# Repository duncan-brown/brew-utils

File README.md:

# brew-utils

Software for a homebrewery dashboard built out of Knight Rider (KITT) dash
replica hardware.

Two Raspberry Pis read temperature probes, flow meters, fermentation
controllers and a keg-monitoring database, and render all of it onto the gauges
of a replica KITT dashboard: the MPH display shows hot liquor tank temperature,
the RPM gauges show serving keezer probes, the LED bargraphs show fermenter
temperatures and how much beer is left in each keg, and the message center
captions whatever the multi-function display is currently showing.

There is a full build write-up, with photos of what every gauge means, at
[Brewery Dashboard on HomebrewTalk](https://www.homebrewtalk.com/threads/brewery-dashboard.726917/).
The physical side — power supply, relays, probes, which wire goes to which pin
on which Pi — is in [HARDWARE.md](HARDWARE.md).

## How it fits together

```
    probes, flow meters, kegs                two Raspberry Pis            KITT dash
    ─────────────────────────                ─────────────────            ─────────
    DS18B20 one-wire probes  ──────────────▶  rpints  ──── serial ────▶  tacho
    RaspberryPints (MySQL)   ──────────────▶          ──── serial ────▶  dummy3, dummy6
                                                 │
                                            GPIO │ mode
                                                 ▼
    DS18B20 one-wire probes  ──────────────▶  brewpi  ──── serial ────▶  speedo
    BrewPi Remix ◀── TiltBridge ◀── Tilt ──▶          ──── serial ────▶  message center
    flow meter relays        ◀──────────────
```

- **`rpints`** runs [RaspberryPints](https://github.com/RaspberryPints/RaspberryPints)
  for keg volume tracking, and owns the dashboard's Power/Auto/Norm/Pursuit
  buttons and the power relays for the whole dash.
- **`brewpi`** runs three instances of [BrewPi Remix](https://github.com/brewpi-remix/brewpi-tools-rmx)
  for fermentation control, which get specific-gravity readings from Tilt
  hydrometers via [TiltBridge](https://github.com/thorrak/tiltbridge).
- The two Pis coordinate over GPIO lines so that pressing Auto, Norm or Pursuit
  on one changes what the other displays and how brightly.
- Both drive the dash boards over serial using Paolo Sancono's KITT protocol.
  The dash electronics themselves are from [ideegeniali](https://www.ideegeniali.it/).

## What's in here

| Path | Status | Description |
| --- | --- | --- |
| [`kitt/`](kitt/) | **in service** | The current system. `panp/panp.py` drives the whole dashboard; `switchpod/` is the Arduino firmware for the dash keypads. See [kitt/README.md](kitt/README.md) for how it works, and [kitt/DASHBOARD.md](kitt/DASHBOARD.md) for what each gauge means. |
| [`schematics/`](schematics/) | reference | KiCad schematics of the control electronics, four sheets generated from the wiring in `HARDWARE.md`; rendered as `images/schematic-*.svg`. |
| `brewpitosmith` | utility | Converts a BrewPi Remix beer log into a CSV that BeerSmith 3 will import, thinned to one row an hour. |
| `images/` | reference | Photographs of the switch pods, the season 2 dash scan, and the `hw-*` photographs of the bench, supply box and control panel that [HARDWARE.md](HARDWARE.md) refers to. |

Two earlier efforts have been archived out of the tree. Each is tagged, so the
whole thing comes back with one command:

| Tag | What it was |
| --- | --- |
| `karr-prototype` | An attempt to rebuild the dash electronics from scratch — four ESP32s driving daisy-chained TLC5940 drivers, with a KiCad board and gerbers. Shelved in 2023 when the ideegeniali boards arrived; never ran the brewery. |
| `pi-temp-display-final` | The predecessor to the KITT dash: seven-segment LEDs multiplexed with pigpio, showing mash temperature and keezer min/max. |

```bash
git checkout karr-prototype -- karr/
```

## Credits

The parts of this system that do the actual work of running the brewery are
other people's: BrewPi Remix by [@LBussy](https://github.com/lbussy), TiltBridge
by [@Thorrak](https://github.com/thorrak), RaspberryPints by
[@RandR+](https://github.com/RandRPints), and the KITT dash boards and serial
protocol by Paolo Sancono at ideegeniali. Thanks also to @day_trippr for help
along the way.

## License

MIT — see [LICENSE](LICENSE).

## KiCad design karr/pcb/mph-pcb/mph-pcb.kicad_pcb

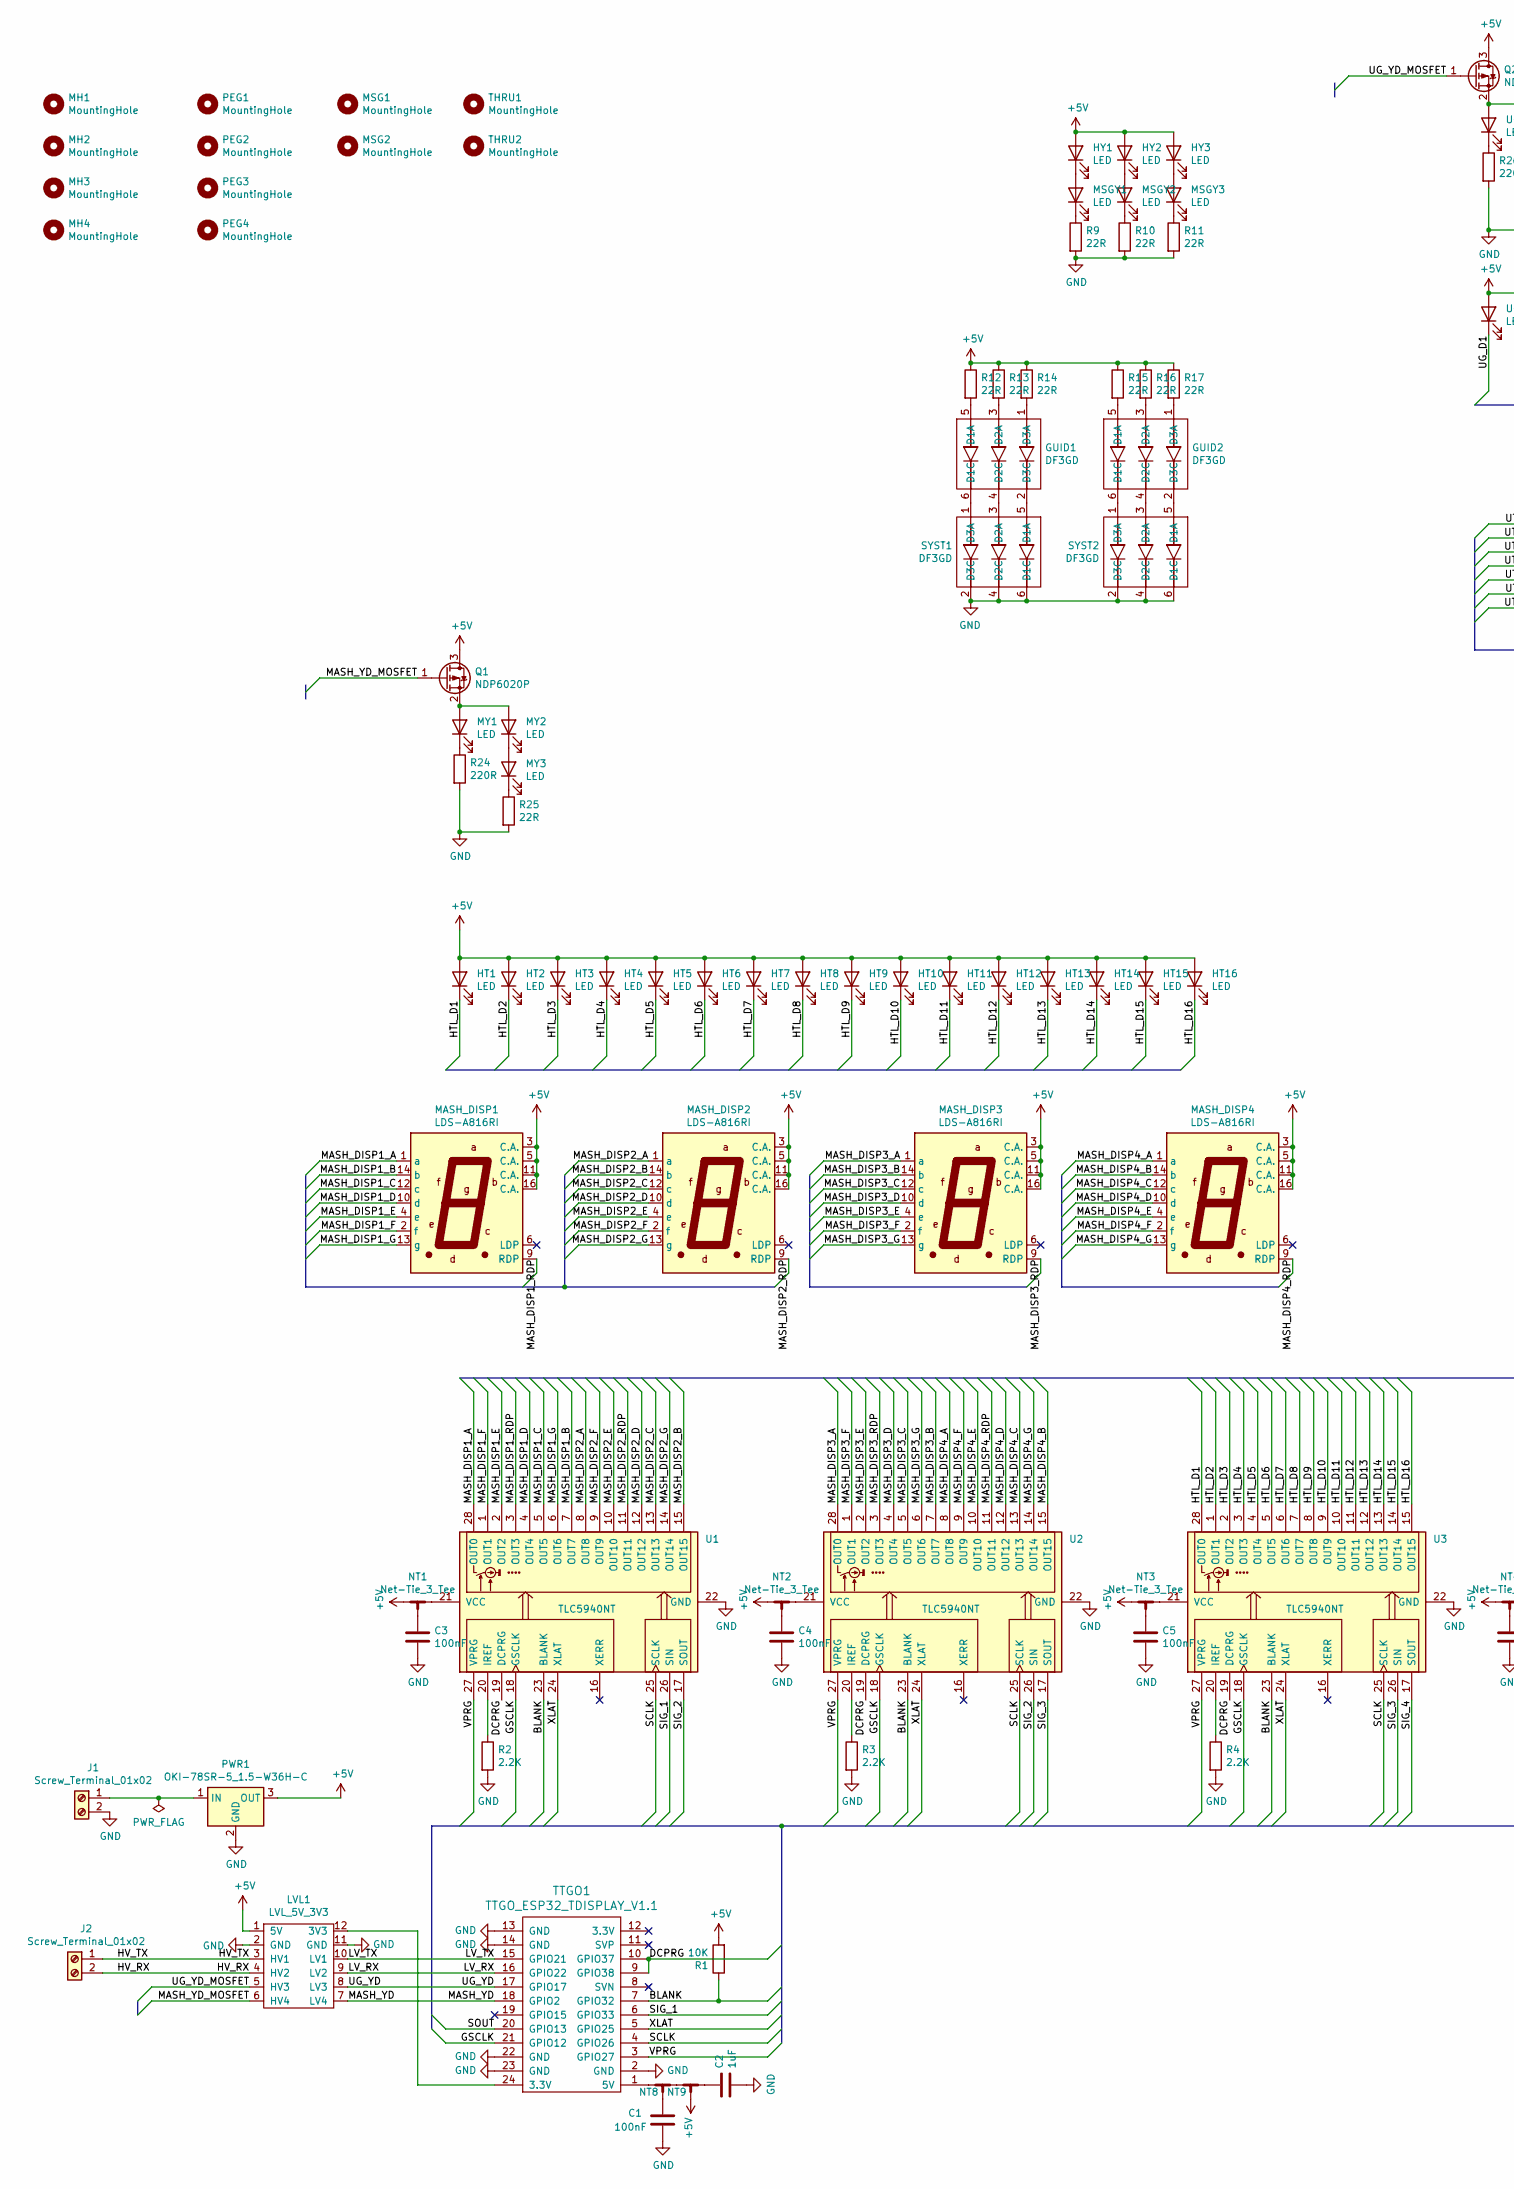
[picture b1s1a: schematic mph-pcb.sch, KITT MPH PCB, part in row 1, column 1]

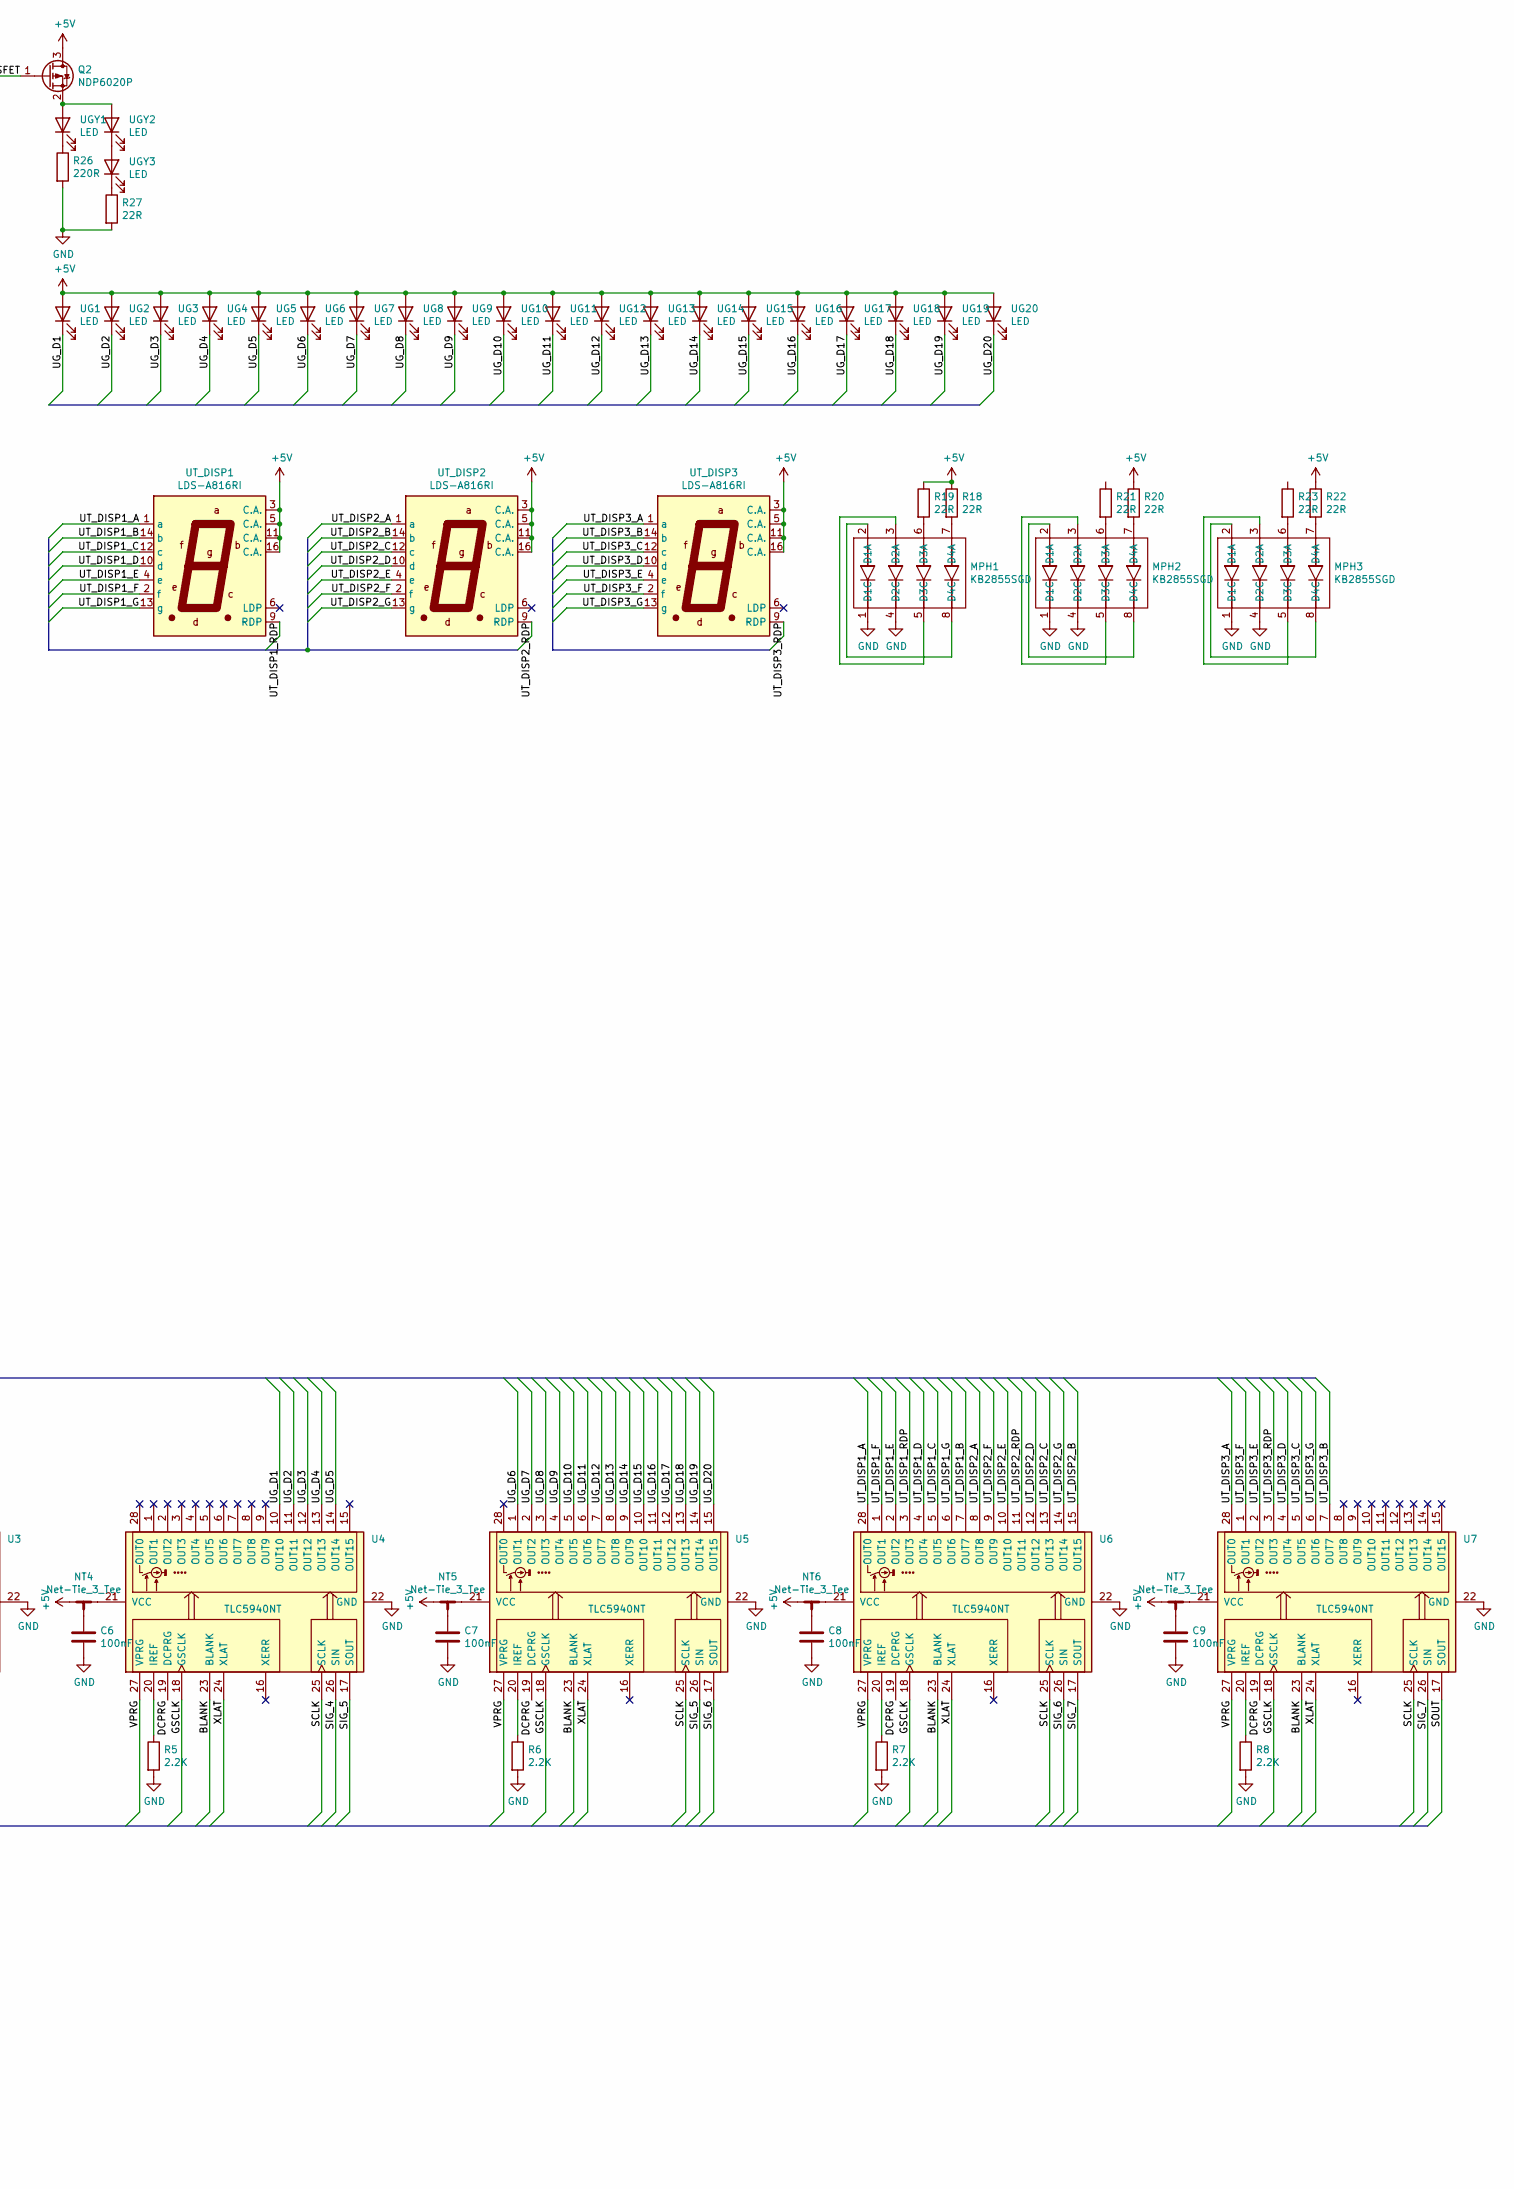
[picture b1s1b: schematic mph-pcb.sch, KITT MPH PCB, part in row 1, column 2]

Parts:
C1, C3, C4, C5, C6, C7, C8, C9: 100nF; C_Rect_L7.0mm_W3.5mm_P5.00mm
C2: 1uF; C_Rect_L7.0mm_W3.5mm_P5.00mm
GUID1, GUID2: DF3GD; DF3GD_Light_Bar
HT1, HT2, HT3, HT4, HT5, HT6, HT7, HT8, HT9, HT10, HT11, HT12, HT13, HT14, HT15, HT16: LED; Flangeless_LED
HY1, HY2, HY3: LED; Flangeless_LED
J1, J2: Screw_Terminal_01x02; 5mm_Screw_Terminal_01x02
LVL1: LVL_5V_3V3
MASH_DISP1, MASH_DISP2, MASH_DISP3, MASH_DISP4: LDS-A816RI
MH1, MH2, MH3, MH4: MountingHole; MountingHole_3.2mm_M3
MPH1, MPH2, MPH3: KB2855SGD; KB2855SGD_Light_Square
MSG1, MSG2: MountingHole; MountingHole_3.2mm_M3
MSGY1, MSGY2, MSGY3: LED; Flangeless_LED
MY1, MY2, MY3: LED; Flangeless_LED
NT1, NT2, NT3, NT4, NT5, NT6, NT7, NT8, NT9: Net-Tie_3_Tee; NetTie-3_THT_Pad0.3mm
PEG1, PEG2, PEG3, PEG4: MountingHole; MountingHole_5.3mm_M5
PWR1: OKI-78SR-5_1.5-W36H-C; Converter_DCDC_muRata_OKI-78SR_Horizontal
Q1, Q2: NDP6020P; TO-220-3_Horizontal_TabDown
R1: 10K; R_Axial_DIN0207_L6.3mm_D2.5mm_P10.16mm_Horizontal
R2, R3, R4, R5, R6, R7, R8: 2.2K; R_Axial_DIN0207_L6.3mm_D2.5mm_P10.16mm_Horizontal
R9, R10, R11, R12, R13, R14, R15, R16, R17, R18, R19, R20, R21, R22, R23, R25, R27: 22R; R_Axial_DIN0207_L6.3mm_D2.5mm_P10.16mm_Horizontal
R24, R26: 220R; R_Axial_DIN0207_L6.3mm_D2.5mm_P10.16mm_Horizontal
SYST1, SYST2: DF3GD; DF3GD_Light_Bar
THRU1, THRU2: MountingHole; MountingHole_6.4mm_M6
TTGO1: TTGO_ESP32_TDISPLAY_V1.1; TTGO_ESP32_TDisplay_v1.1
U1, U2, U3, U4, U5, U6, U7: TLC5940NT; DIP-28_W7.62mm
UG1, UG2, UG3, UG4, UG5, UG6, UG7, UG8, UG9, UG10, UG11, UG12, UG13, UG14, UG15, UG16, UG17, UG18, UG19, UG20: LED; Flangeless_LED
UGY1, UGY2, UGY3: LED; Flangeless_LED
UT_DISP1, UT_DISP2, UT_DISP3: LDS-A816RI

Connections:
+5V: HT1.2 (A), HT2.2 (A), HT3.2 (A), HT4.2 (A), HT5.2 (A), HT6.2 (A), HT7.2 (A), HT8.2 (A), HT9.2 (A), HT10.2 (A), HT11.2 (A), HT12.2 (A), HT13.2 (A), HT14.2 (A), HT15.2 (A), HT16.2 (A), HY1.2 (A), HY2.2 (A), HY3.2 (A), LVL1.1 (5V), MASH_DISP1.3 (C.A.), MASH_DISP1.5 (C.A.), MASH_DISP1.11 (C.A.), MASH_DISP1.16 (C.A.), MASH_DISP2.3 (C.A.), MASH_DISP2.5 (C.A.), MASH_DISP2.11 (C.A.), MASH_DISP2.16 (C.A.), MASH_DISP3.3 (C.A.), MASH_DISP3.5 (C.A.), MASH_DISP3.11 (C.A.), MASH_DISP3.16 (C.A.), MASH_DISP4.3 (C.A.), MASH_DISP4.5 (C.A.), MASH_DISP4.11 (C.A.), MASH_DISP4.16 (C.A.), NT1.1, NT2.1, NT3.1, NT4.1, NT5.1, NT6.1, NT7.1, NT9.3, PWR1.3 (OUT), Q1.3 (D), Q2.3 (D), R1.2, R12.1, R13.1, R14.1, R15.1, R16.1, R17.1, R18.1, R19.1, R20.1, R22.1, UG1.2 (A), UG2.2 (A), UG3.2 (A), UG4.2 (A), UG5.2 (A), UG6.2 (A), UG7.2 (A), UG8.2 (A), UG9.2 (A), UG10.2 (A), UG11.2 (A), UG12.2 (A), UG13.2 (A), UG14.2 (A), UG15.2 (A), UG16.2 (A), UG17.2 (A), UG18.2 (A), UG19.2 (A), UG20.2 (A), UT_DISP1.3 (C.A.), UT_DISP1.5 (C.A.), UT_DISP1.11 (C.A.), UT_DISP1.16 (C.A.), UT_DISP2.3 (C.A.), UT_DISP2.5 (C.A.), UT_DISP2.11 (C.A.), UT_DISP2.16 (C.A.), UT_DISP3.3 (C.A.), UT_DISP3.5 (C.A.), UT_DISP3.11 (C.A.), UT_DISP3.16 (C.A.)
/BLANK: R1.1, TTGO1.7 (GPIO32), U1.23 (BLANK), U2.23 (BLANK), U3.23 (BLANK), U4.23 (BLANK), U5.23 (BLANK), U6.23 (BLANK), U7.23 (BLANK)
/DCPRG: TTGO1.9 (GPIO38), TTGO1.10 (GPIO37), U1.19 (DCPRG), U2.19 (DCPRG), U3.19 (DCPRG), U4.19 (DCPRG), U5.19 (DCPRG), U6.19 (DCPRG), U7.19 (DCPRG)
/GSCLK: TTGO1.21 (GPIO12), U1.18 (GSCLK), U2.18 (GSCLK), U3.18 (GSCLK), U4.18 (GSCLK), U5.18 (GSCLK), U6.18 (GSCLK), U7.18 (GSCLK)
/HTL_D1: HT1.1 (K), U3.28 (OUT0)
/HTL_D2: HT2.1 (K), U3.1 (OUT1)
/HTL_D3: HT3.1 (K), U3.2 (OUT2)
/HTL_D4: HT4.1 (K), U3.3 (OUT3)
/HTL_D5: HT5.1 (K), U3.4 (OUT4)
/HTL_D6: HT6.1 (K), U3.5 (OUT5)
/HTL_D7: HT7.1 (K), U3.6 (OUT6)
/HTL_D8: HT8.1 (K), U3.7 (OUT7)
/HTL_D9: HT9.1 (K), U3.8 (OUT8)
/HTL_D10: HT10.1 (K), U3.9 (OUT9)
/HTL_D11: HT11.1 (K), U3.10 (OUT10)
/HTL_D12: HT12.1 (K), U3.11 (OUT11)
/HTL_D13: HT13.1 (K), U3.12 (OUT12)
/HTL_D14: HT14.1 (K), U3.13 (OUT13)
/HTL_D15: HT15.1 (K), U3.14 (OUT14)
/HTL_D16: HT16.1 (K), U3.15 (OUT15)
/HV_RX: J2.2, LVL1.4 (HV2)
/HV_TX: J2.1, LVL1.3 (HV1)
/LV_RX: LVL1.9 (LV2), TTGO1.16 (GPIO22)
/LV_TX: LVL1.10 (LV1), TTGO1.15 (GPIO21)
/MASH_DISP1_A: MASH_DISP1.1 (a), U1.28 (OUT0)
/MASH_DISP1_B: MASH_DISP1.14 (b), U1.7 (OUT7)
/MASH_DISP1_C: MASH_DISP1.12 (c), U1.5 (OUT5)
/MASH_DISP1_D: MASH_DISP1.10 (d), U1.4 (OUT4)
/MASH_DISP1_E: MASH_DISP1.4 (e), U1.2 (OUT2)
/MASH_DISP1_F: MASH_DISP1.2 (f), U1.1 (OUT1)
/MASH_DISP1_G: MASH_DISP1.13 (g), U1.6 (OUT6)
/MASH_DISP1_RDP: MASH_DISP1.9 (RDP), U1.3 (OUT3)
/MASH_DISP2_A: MASH_DISP2.1 (a), U1.8 (OUT8)
/MASH_DISP2_B: MASH_DISP2.14 (b), U1.15 (OUT15)
/MASH_DISP2_C: MASH_DISP2.12 (c), U1.13 (OUT13)
/MASH_DISP2_D: MASH_DISP2.10 (d), U1.12 (OUT12)
/MASH_DISP2_E: MASH_DISP2.4 (e), U1.10 (OUT10)
/MASH_DISP2_F: MASH_DISP2.2 (f), U1.9 (OUT9)
/MASH_DISP2_G: MASH_DISP2.13 (g), U1.14 (OUT14)
/MASH_DISP2_RDP: MASH_DISP2.9 (RDP), U1.11 (OUT11)
/MASH_DISP3_A: MASH_DISP3.1 (a), U2.28 (OUT0)
/MASH_DISP3_B: MASH_DISP3.14 (b), U2.7 (OUT7)
/MASH_DISP3_C: MASH_DISP3.12 (c), U2.5 (OUT5)
/MASH_DISP3_D: MASH_DISP3.10 (d), U2.4 (OUT4)
/MASH_DISP3_E: MASH_DISP3.4 (e), U2.2 (OUT2)
/MASH_DISP3_F: MASH_DISP3.2 (f), U2.1 (OUT1)
/MASH_DISP3_G: MASH_DISP3.13 (g), U2.6 (OUT6)
/MASH_DISP3_RDP: MASH_DISP3.9 (RDP), U2.3 (OUT3)
/MASH_DISP4_A: MASH_DISP4.1 (a), U2.8 (OUT8)
/MASH_DISP4_B: MASH_DISP4.14 (b), U2.15 (OUT15)
/MASH_DISP4_C: MASH_DISP4.12 (c), U2.13 (OUT13)
/MASH_DISP4_D: MASH_DISP4.10 (d), U2.12 (OUT12)
/MASH_DISP4_E: MASH_DISP4.4 (e), U2.10 (OUT10)
/MASH_DISP4_F: MASH_DISP4.2 (f), U2.9 (OUT9)
/MASH_DISP4_G: MASH_DISP4.13 (g), U2.14 (OUT14)
/MASH_DISP4_RDP: MASH_DISP4.9 (RDP), U2.11 (OUT11)
/MASH_YD: LVL1.7 (LV4), TTGO1.18 (GPIO2)
/MASH_YD_MOSFET: LVL1.6 (HV4), Q1.1 (G)
/SCLK: TTGO1.4 (GPIO26), U1.25 (SCLK), U2.25 (SCLK), U3.25 (SCLK), U4.25 (SCLK), U5.25 (SCLK), U6.25 (SCLK), U7.25 (SCLK)
/SIG_1: TTGO1.6 (GPIO33), U1.26 (SIN)
/SIG_2: U1.17 (SOUT), U2.26 (SIN)
/SIG_3: U2.17 (SOUT), U3.26 (SIN)
/SIG_4: U3.17 (SOUT), U4.26 (SIN)
/SIG_5: U4.17 (SOUT), U5.26 (SIN)
/SIG_6: U5.17 (SOUT), U6.26 (SIN)
/SIG_7: U6.17 (SOUT), U7.26 (SIN)
/SOUT: TTGO1.20 (GPIO13), U7.17 (SOUT)
/UG_D1: U4.10 (OUT10), UG1.1 (K)
/UG_D2: U4.11 (OUT11), UG2.1 (K)
/UG_D3: U4.12 (OUT12), UG3.1 (K)
/UG_D4: U4.13 (OUT13), UG4.1 (K)
/UG_D5: U4.14 (OUT14), UG5.1 (K)
/UG_D6: U5.1 (OUT1), UG6.1 (K)
/UG_D7: U5.2 (OUT2), UG7.1 (K)
/UG_D8: U5.3 (OUT3), UG8.1 (K)
/UG_D9: U5.4 (OUT4), UG9.1 (K)
/UG_D10: U5.5 (OUT5), UG10.1 (K)
/UG_D11: U5.6 (OUT6), UG11.1 (K)
/UG_D12: U5.7 (OUT7), UG12.1 (K)
/UG_D13: U5.8 (OUT8), UG13.1 (K)
/UG_D14: U5.9 (OUT9), UG14.1 (K)
/UG_D15: U5.10 (OUT10), UG15.1 (K)
/UG_D16: U5.11 (OUT11), UG16.1 (K)
/UG_D17: U5.12 (OUT12), UG17.1 (K)
/UG_D18: U5.13 (OUT13), UG18.1 (K)
/UG_D19: U5.14 (OUT14), UG19.1 (K)
/UG_D20: U5.15 (OUT15), UG20.1 (K)
/UG_YD: LVL1.8 (LV3), TTGO1.17 (GPIO17)
/UG_YD_MOSFET: LVL1.5 (HV3), Q2.1 (G)
/UT_DISP1_A: U6.28 (OUT0), UT_DISP1.1 (a)
/UT_DISP1_B: U6.7 (OUT7), UT_DISP1.14 (b)
/UT_DISP1_C: U6.5 (OUT5), UT_DISP1.12 (c)
/UT_DISP1_D: U6.4 (OUT4), UT_DISP1.10 (d)
/UT_DISP1_E: U6.2 (OUT2), UT_DISP1.4 (e)
/UT_DISP1_F: U6.1 (OUT1), UT_DISP1.2 (f)
/UT_DISP1_G: U6.6 (OUT6), UT_DISP1.13 (g)
/UT_DISP1_RDP: U6.3 (OUT3), UT_DISP1.9 (RDP)
/UT_DISP2_A: U6.8 (OUT8), UT_DISP2.1 (a)
/UT_DISP2_B: U6.15 (OUT15), UT_DISP2.14 (b)
/UT_DISP2_C: U6.13 (OUT13), UT_DISP2.12 (c)
/UT_DISP2_D: U6.12 (OUT12), UT_DISP2.10 (d)
/UT_DISP2_E: U6.10 (OUT10), UT_DISP2.4 (e)
/UT_DISP2_F: U6.9 (OUT9), UT_DISP2.2 (f)
/UT_DISP2_G: U6.14 (OUT14), UT_DISP2.13 (g)
/UT_DISP2_RDP: U6.11 (OUT11), UT_DISP2.9 (RDP)
/UT_DISP3_A: U7.28 (OUT0), UT_DISP3.1 (a)
/UT_DISP3_B: U7.7 (OUT7), UT_DISP3.14 (b)
/UT_DISP3_C: U7.5 (OUT5), UT_DISP3.12 (c)
/UT_DISP3_D: U7.4 (OUT4), UT_DISP3.10 (d)
/UT_DISP3_E: U7.2 (OUT2), UT_DISP3.4 (e)
/UT_DISP3_F: U7.1 (OUT1), UT_DISP3.2 (f)
/UT_DISP3_G: U7.6 (OUT6), UT_DISP3.13 (g)
/UT_DISP3_RDP: U7.3 (OUT3), UT_DISP3.9 (RDP)
/VPRG: TTGO1.3 (GPIO27), U1.27 (VPRG), U2.27 (VPRG), U3.27 (VPRG), U4.27 (VPRG), U5.27 (VPRG), U6.27 (VPRG), U7.27 (VPRG)
/XLAT: TTGO1.5 (GPIO25), U1.24 (XLAT), U2.24 (XLAT), U3.24 (XLAT), U4.24 (XLAT), U5.24 (XLAT), U6.24 (XLAT), U7.24 (XLAT)
GND: C1.2, C2.2, C3.2, C4.2, C5.2, C6.2, C7.2, C8.2, C9.2, J1.2, LVL1.2 (GND), LVL1.11 (GND), MPH1.1 (D1C), MPH1.4 (D2C), MPH2.1 (D1C), MPH2.4 (D2C), MPH3.1 (D1C), MPH3.4 (D2C), PWR1.2 (GND), R2.2, R3.2, R4.2, R5.2, R6.2, R7.2, R8.2, R9.2, R10.2, R11.2, R24.2, R25.2, R26.2, R27.2, SYST1.2 (D3C), SYST1.4 (D2C), SYST1.6 (D1C), SYST2.2 (D3C), SYST2.4 (D2C), SYST2.6 (D1C), TTGO1.2 (GND), TTGO1.13 (GND), TTGO1.14 (GND), TTGO1.22 (GND), TTGO1.23 (GND), U1.22 (GND), U2.22 (GND), U3.22 (GND), U4.22 (GND), U5.22 (GND), U6.22 (GND), U7.22 (GND)
unnamed: C1.1, NT8.3
unnamed: C2.1, NT9.1
unnamed: C3.1, NT1.3
unnamed: C4.1, NT2.3
unnamed: C5.1, NT3.3
unnamed: C6.1, NT4.3
unnamed: C7.1, NT5.3
unnamed: C8.1, NT6.3
unnamed: C9.1, NT7.3
unnamed: GUID1.1 (D3A), R14.2
unnamed: GUID1.2 (D3C), SYST1.5 (D1A)
unnamed: GUID1.3 (D2A), R13.2
unnamed: GUID1.4 (D2C), SYST1.3 (D2A)
unnamed: GUID1.5 (D1A), R12.2
unnamed: GUID1.6 (D1C), SYST1.1 (D3A)
unnamed: GUID2.1 (D3A), R17.2
unnamed: GUID2.2 (D3C), SYST2.5 (D1A)
unnamed: GUID2.3 (D2A), R16.2
unnamed: GUID2.4 (D2C), SYST2.3 (D2A)
unnamed: GUID2.5 (D1A), R15.2
unnamed: GUID2.6 (D1C), SYST2.1 (D3A)
unnamed: HY1.1 (K), MSGY1.2 (A)
unnamed: HY2.1 (K), MSGY2.2 (A)
unnamed: HY3.1 (K), MSGY3.2 (A)
unnamed: J1.1, PWR1.1 (IN)
unnamed: LVL1.12 (3V3), TTGO1.24 (3.3V)
unnamed: MPH1.2 (D1A), MPH1.8 (D4C)
unnamed: MPH1.3 (D2A), MPH1.5 (D3C)
unnamed: MPH1.6 (D3A), R19.2
unnamed: MPH1.7 (D4A), R18.2
unnamed: MPH2.2 (D1A), MPH2.8 (D4C)
unnamed: MPH2.3 (D2A), MPH2.5 (D3C)
unnamed: MPH2.6 (D3A), R21.2
unnamed: MPH2.7 (D4A), R20.2
unnamed: MPH3.2 (D1A), MPH3.8 (D4C)
unnamed: MPH3.3 (D2A), MPH3.5 (D3C)
unnamed: MPH3.6 (D3A), R23.2
unnamed: MPH3.7 (D4A), R22.2
unnamed: MSGY1.1 (K), R9.1
unnamed: MSGY2.1 (K), R10.1
unnamed: MSGY3.1 (K), R11.1
unnamed: MY1.1 (K), R24.1
unnamed: MY1.2 (A), MY2.2 (A), Q1.2 (S)
unnamed: MY2.1 (K), MY3.2 (A)
unnamed: MY3.1 (K), R25.1
unnamed: NT1.2, U1.21 (VCC)
unnamed: NT2.2, U2.21 (VCC)
unnamed: NT3.2, U3.21 (VCC)
unnamed: NT4.2, U4.21 (VCC)
unnamed: NT5.2, U5.21 (VCC)
unnamed: NT6.2, U6.21 (VCC)
unnamed: NT7.2, U7.21 (VCC)
unnamed: NT8.1, TTGO1.1 (5V)
unnamed: NT8.2, NT9.2
unnamed: Q2.2 (S), UGY1.2 (A), UGY2.2 (A)
unnamed: R2.1, U1.20 (IREF)
unnamed: R3.1, U2.20 (IREF)
unnamed: R4.1, U3.20 (IREF)
unnamed: R5.1, U4.20 (IREF)
unnamed: R6.1, U5.20 (IREF)
unnamed: R7.1, U6.20 (IREF)
unnamed: R8.1, U7.20 (IREF)
unnamed: R26.1, UGY1.1 (K)
unnamed: R27.1, UGY3.1 (K)
unnamed: UGY2.1 (K), UGY3.2 (A)

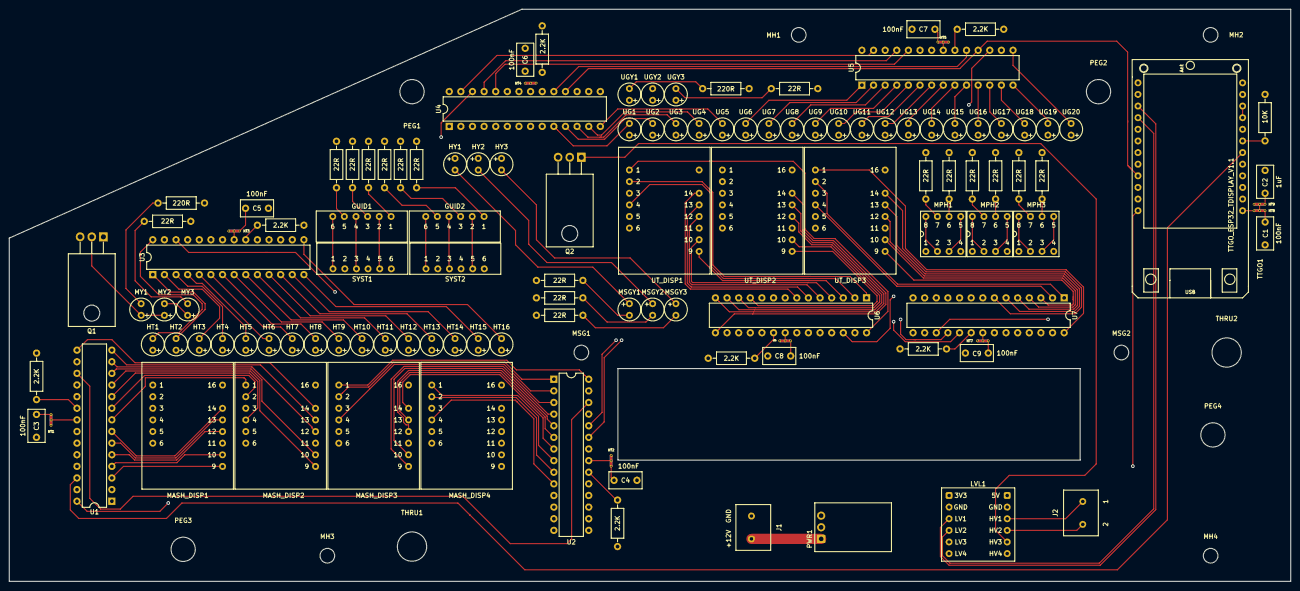
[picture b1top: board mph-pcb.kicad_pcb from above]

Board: 4 copper layers, 280.0 x 125.0 mm, 133 parts (0 on the bottom side), 181 nets.

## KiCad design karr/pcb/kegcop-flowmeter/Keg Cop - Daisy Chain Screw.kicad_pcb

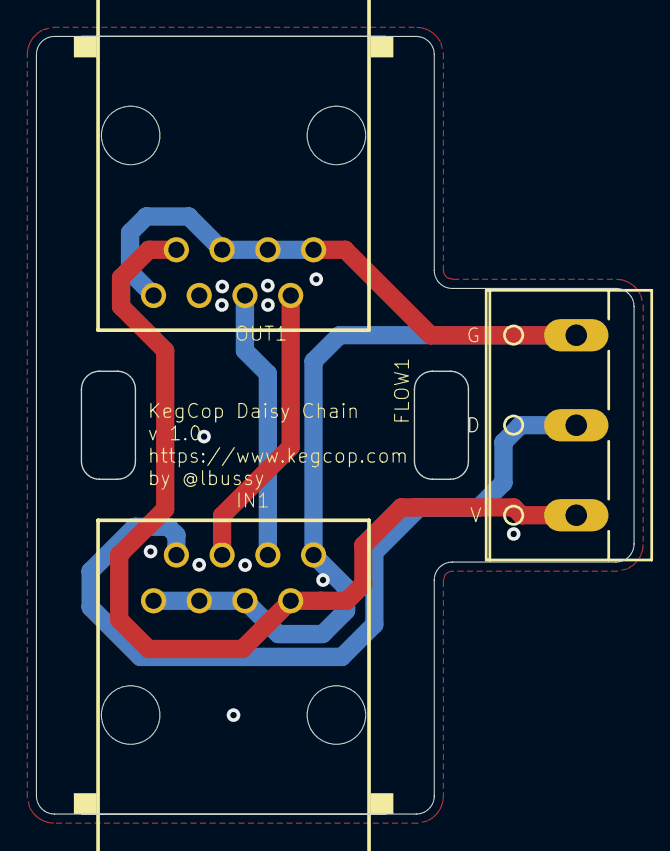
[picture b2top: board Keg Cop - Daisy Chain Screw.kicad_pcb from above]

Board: 2 copper layers, 33.2 x 43.2 mm, 3 parts (0 on the bottom side), 5 nets.

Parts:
FLOW1: W237-103
IN1: RJ45; RJ45-NO-SHIELD
OUT1: RJ45; RJ45-NO-SHIELD

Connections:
/5VD: FLOW1.1, IN1.7, OUT1.7
/DATA0: FLOW1.2, IN1.2
/GND: FLOW1.3, IN1.1, IN1.3, IN1.5, IN1.8, OUT1.1, OUT1.3, OUT1.5, OUT1.8
unnamed: IN1.4, OUT1.2
unnamed: IN1.6, OUT1.4
